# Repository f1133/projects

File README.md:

# projects

A workspace repository for assorted projects.

## About

This repository is a starting point. Each project lives in its own
subdirectory with its own README describing what it does and how to
run it.

## Getting started

```bash
git clone https://github.com/f1133/projects.git
cd projects
```

## Layout

```
projects/
├── README.md
├── hardware/
│   └── g431-can-actuator/   # STM32G431 CAN-FD actuator node (KiCad) + perf-board prototype plans
└── <project-name>/          # one directory per project
```

## Projects

| Project | Description |
|---|---|
| [`hardware/g431-can-actuator`](hardware/g431-can-actuator) | KiCad schematic for a CAN-FD BLDC actuator node: STM32G431CBT6 + DRV8311S three-phase driver, one board per actuator, daisy-chained on a single CAN bus. `proto/` holds the perf-board prototype layouts (placement and wiring pictures, wiring lists, BOMs). |

## License

No license has been chosen yet. Until one is added, all rights are
reserved by the repository owner.

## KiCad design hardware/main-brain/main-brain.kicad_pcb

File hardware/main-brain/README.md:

# main-brain

ESP32-S3 controller for the base. Two I2C devices, two microphones on a shared
clock, the hardware kill line and the power chain — everything that does not
move. 140 x 70 mm.

Generated from the Juno build console's base wiring. Schematic and PCB are
complete through placement, netclasses and design rules. **No copper is
routed.**

## Why the board is this wide

The microphones set it. A6 and A7 sit at x = 5 mm and x = 135 mm, exactly
130 mm apart, because that spacing is what turns two microphones into a
bearing. Both share BCLK and WS and both drive the same data pin; A6 has L/R
tied low and A7 tied high, and that is what makes them stereo.

## Before you route

**The ESP32-S3 Super Mini footprint is unverified.** External sources for this
board were unreachable from the environment this was generated in, so
`ESP32_S3_LEFT` / `ESP32_S3_RIGHT` in `tools/modules.py` hold the conventional
2 x 11 Super Mini arrangement and nothing stronger. Check it against your actual
board before ordering. The schematic is correct regardless — nets are by pin
name — so if the order is wrong, correcting those two lists and re-running
`build.py` is the whole fix. Same applies to the MP1584EN, the mic breakouts and
the I2C modules, though those are more standard.

## Indicators

Two, both XL-3216SURC red 1206, the part you have. D2 sits on the **5 V** rail
rather than 3.3 V so it reports the buck, which is the thing that actually
fails - the S3's own regulator is downstream of it. D3 is a firmware heartbeat
on IO1; the module has an LED on IO48 but it is buried once the board is in the
base.

Series resistors follow the part's 2.4 V forward drop: 470 R on the 5 V rail
and 220 R on the 3.3 V GPIO, both giving about 4-5 mA.

## One part added beyond the console BOM

**D1, a 10 V zener, plus R6.** The console specifies an SI2301-class P-MOSFET
for reverse-polarity protection straight off a 19 V input. That part is rated
around ±8 V gate-source, so an unclamped gate destroys it on first power-up.
R6 pulls the gate down and D1 clamps Vgs. Without these the protection circuit
is the thing that fails.

## One thing worth changing, not changed

The kill line works by pulling the shared EN wire low with Q2, while each node's
PB12 drives that same wire high push-pull. Killing therefore shorts three MCU
outputs to ground through Q2 — within ratings (about 60 mA total, Q2 handles
200 mA) but poor practice, and the node cannot tell it has been killed.

Two clean fixes: a series resistor between PB12 and the EN net on each node
board, or drive PB12 open-drain in firmware. It is left as the console
specifies because changing it is a design decision, not a transcription.

## Pin assignment

Follows `06_electrical.md`. GPIO 3 is left free as a strapping pin. CAN is on
GPIO 5/6 — the docs say "UART or CAN" without saying which is TX, so TX is 5 and
RX is 6; the TWAI controller maps to any GPIO, so swap in firmware if needed.

| GPIO | Use |
|---|---|
| 2 | I2S DIN, both mics |
| 4 | I2S DOUT, to the speaker amp on J4 |
| 5 / 6 | CAN TX / RX |
| 7 | kill line to Q2 |
| 8 / 9 | I2C SDA / SCL |
| 13 | ToF INT |
| 43 / 44 | I2S BCLK / WS |

I2C pull-ups (R1, R2, 2k2) are here and only here — the master end, as the
wiring rules require.

## Ports

| Ref | Port | Pins |
|---|---|---|
| J1 | 19 V barrel jack | star ground lands here |
| J2 | CAN + power to the arm | CANH, CANL, EN, 5 V, GND |
| J3 | 19 V to the arm | +19 V, GND |
| J4 | I2S to the speaker amp | 5 V, GND, DOUT, BCLK, WS |

J4 exists because GPIO 4 is assigned to a speaker amp that the BOM places in the
head while also saying it shares the mic I2S bus — and I2S does not travel over
CAN. The header puts the signal somewhere real; where the amp physically lives
is your call.

## Verification status

ERC and DRC have **not** been run. `tools/check.py` verifies 96 pad nets, 96
schematic stubs against their pin endpoints, courtyard collisions and the board
outline, and every file round-trips through `kiutils`. Run ERC and DRC locally
before ordering.

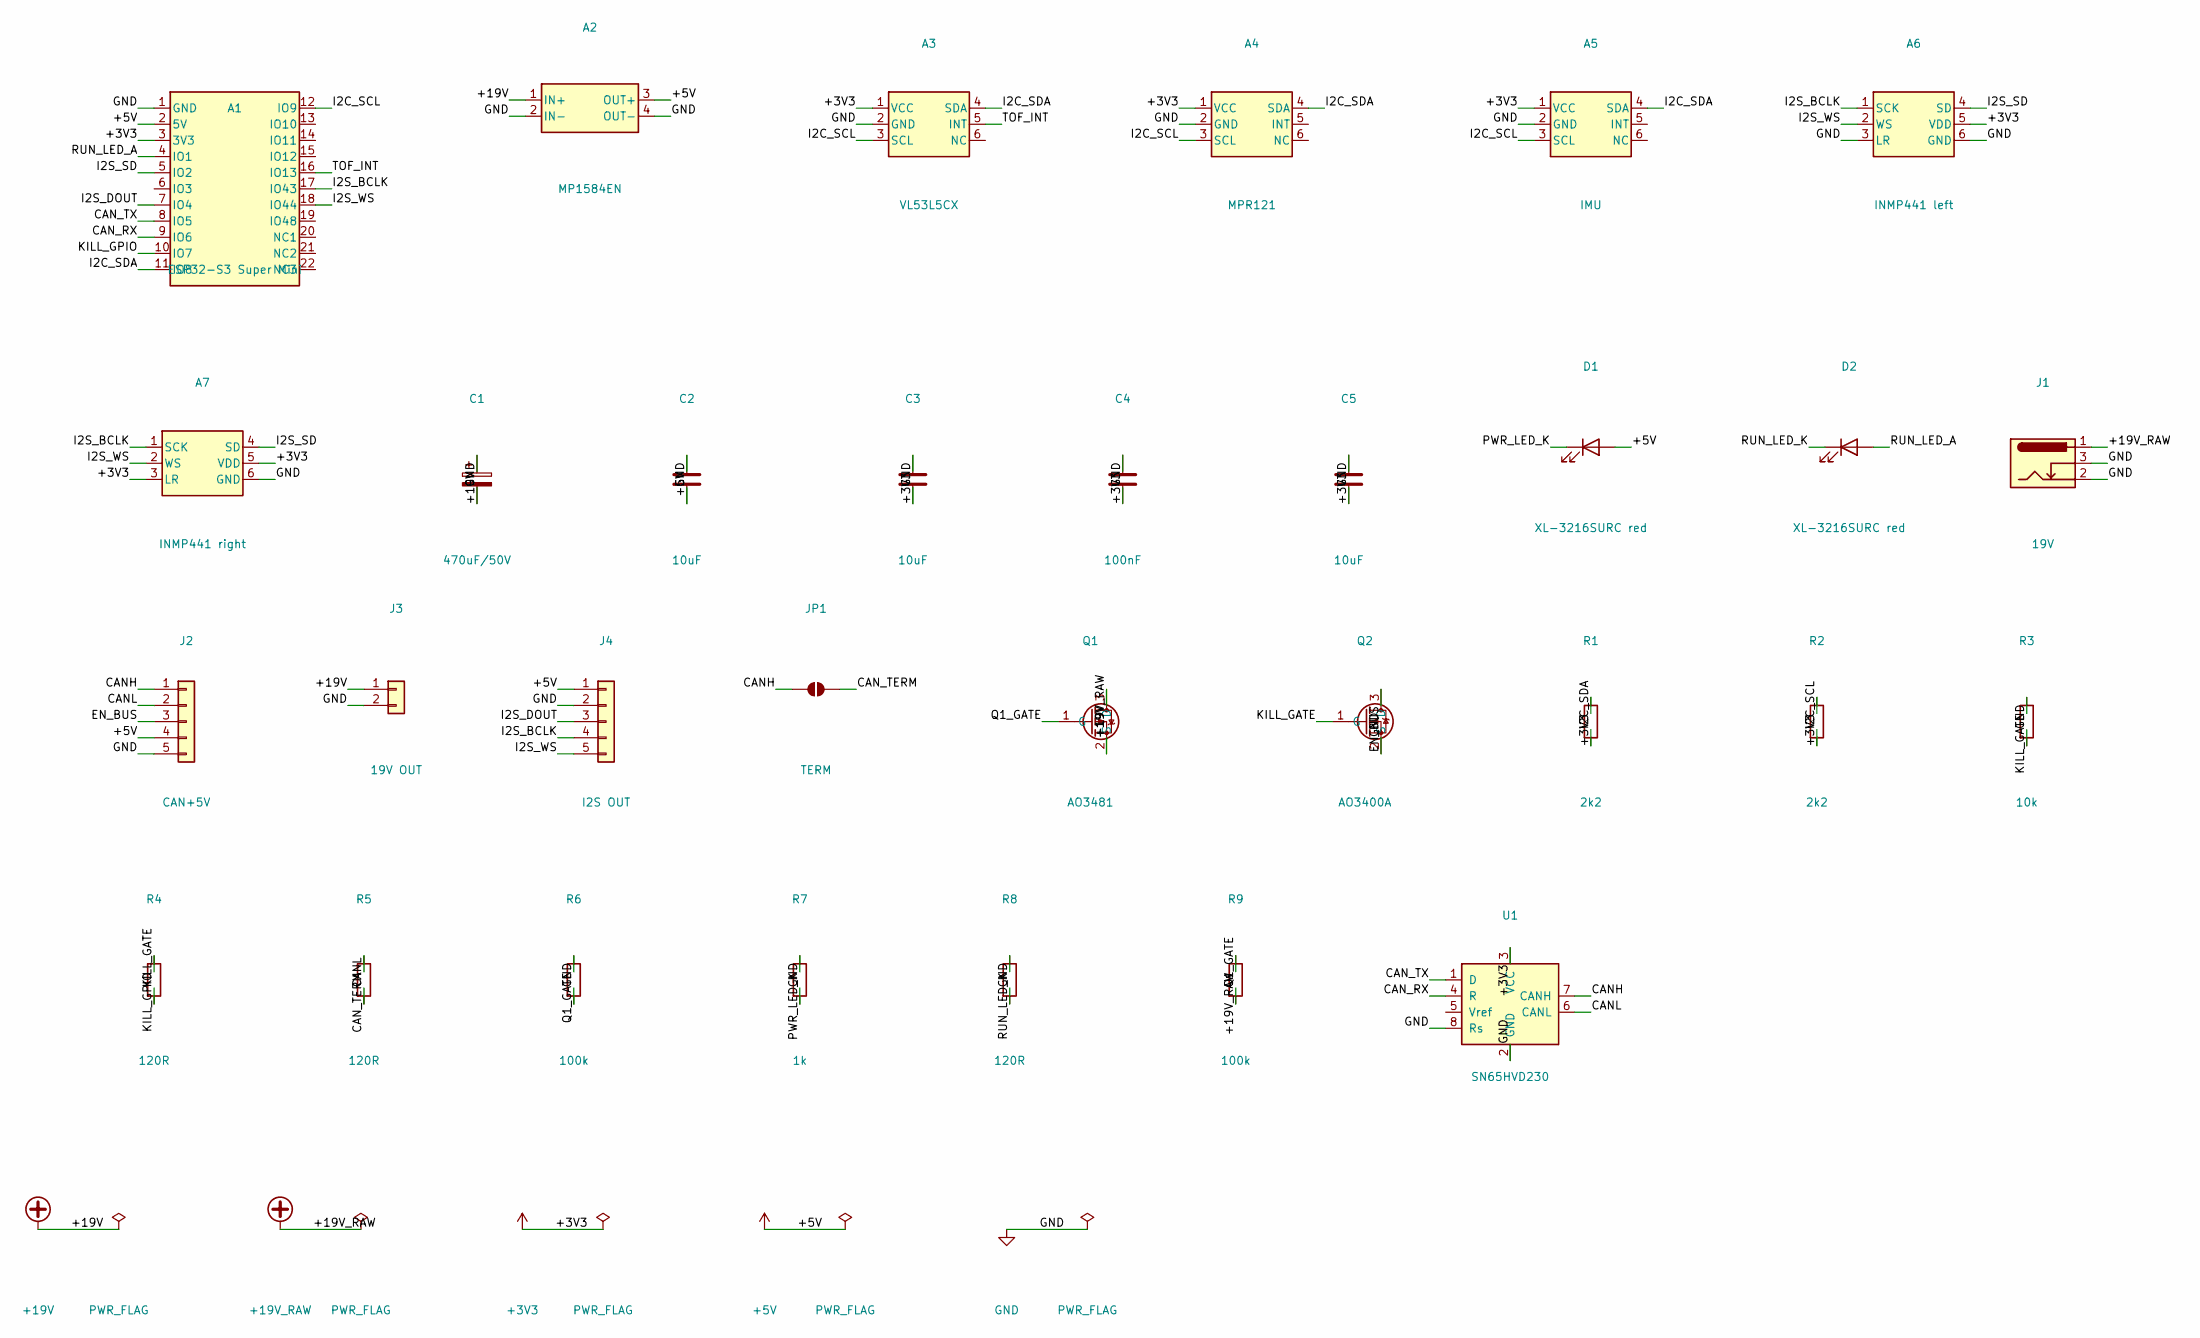
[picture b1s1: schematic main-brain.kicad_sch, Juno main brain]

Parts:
A1: ESP32-S3 Super Mini; ESP32_S3_SuperMini_Socket
A2: MP1584EN; MP1584EN_Module
A3: VL53L5CX; Module_1x06_2.54
A4: MPR121; Module_1x06_2.54
A5: IMU; Module_1x06_2.54
A6: INMP441 left; Module_1x06_2.54
A7: INMP441 right; Module_1x06_2.54
C1: 470uF/50V; CP_Elec_10x10.5
C2, C3, C5: 10uF; C_1206_3216Metric
C4: 100nF; C_1206_3216Metric
D1, D2: XL-3216SURC red; LED_1206_3216Metric
J1: 19V; BarrelJack_CUI_PJ-102AH_Horizontal
J2: CAN+5V; JST_XH_S5B-XH-A_1x05_P2.50mm_Horizontal
J3: 19V OUT; JST_VH_S2P-VH_1x02_P3.96mm_Horizontal
J4: I2S OUT; PinHeader_1x05_P2.54mm_Vertical
JP1: TERM; SolderJumper-2_P1.3mm_Open_Pad1.0x1.5mm
Q1: AO3481; SOT-23
Q2: AO3400A; SOT-23
R1, R2: 2k2; R_1206_3216Metric
R3: 10k; R_1206_3216Metric
R4, R5, R8: 120R; R_1206_3216Metric
R6, R9: 100k; R_1206_3216Metric
R7: 1k; R_1206_3216Metric
U1: SN65HVD230; SOIC-8_3.9x4.9mm_P1.27mm

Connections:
+3V3: A1.3 (3V3), A3.1 (VCC), A4.1 (VCC), A5.1 (VCC), A6.5 (VDD), A7.3 (LR), A7.5 (VDD), C3.1, C4.1, C5.1, R1.1, R2.1, U1.3 (VCC)
+5V: A1.2 (5V), A2.3 (OUT+), C2.1, D1.2 (A), J2.4, J4.1
+19V: A2.1 (IN+), C1.1, J3.1, Q1.3 (D)
+19V_RAW: J1.1, Q1.2 (S), R9.1
CANH: J2.1, JP1.1 (A), U1.7 (CANH)
CANL: J2.2, R5.2, U1.6 (CANL)
CAN_RX: A1.9 (IO6), U1.4 (R)
CAN_TERM: JP1.2 (B), R5.1
CAN_TX: A1.8 (IO5), U1.1 (D)
EN_BUS: J2.3, Q2.3 (D)
GND: A1.1 (GND), A2.2 (IN-), A2.4 (OUT-), A3.2 (GND), A4.2 (GND), A5.2 (GND), A6.3 (LR), A6.6 (GND), A7.6 (GND), C1.2, C2.2, C3.2, C4.2, C5.2, J1.2, J1.3, J2.5, J3.2, J4.2, Q2.2 (S), R3.2, R6.2, R7.2, R8.2, U1.2 (GND), U1.8 (Rs)
I2C_SCL: A1.12 (IO9), A3.3 (SCL), A4.3 (SCL), A5.3 (SCL), R2.2
I2C_SDA: A1.11 (IO8), A3.4 (SDA), A4.4 (SDA), A5.4 (SDA), R1.2
I2S_BCLK: A1.17 (IO43), A6.1 (SCK), A7.1 (SCK), J4.4
I2S_DOUT: A1.7 (IO4), J4.3
I2S_SD: A1.5 (IO2), A6.4 (SD), A7.4 (SD)
I2S_WS: A1.18 (IO44), A6.2 (WS), A7.2 (WS), J4.5
KILL_GATE: Q2.1 (G), R3.1, R4.2
KILL_GPIO: A1.10 (IO7), R4.1
PWR_LED_K: D1.1 (K), R7.1
Q1_GATE: Q1.1 (G), R6.1, R9.2
RUN_LED_A: A1.4 (IO1), D2.2 (A)
RUN_LED_K: D2.1 (K), R8.1
TOF_INT: A1.16 (IO13), A3.5 (INT)

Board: 2 copper layers, 31 parts (0 on the bottom side), 24 nets, no tracks yet.

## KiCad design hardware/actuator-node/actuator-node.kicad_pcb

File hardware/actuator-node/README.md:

# actuator-node

STM32G431CBT6 CAN-FD joint controller. One per joint; the boards daisy-chain on
a single CAN bus and are addressed by three solder jumpers. 70 x 60 mm.

Parts are placed by functional block - see `placement.svg` for the colour-coded
map. Each block keeps its own passives: the CAN transceiver with its
termination and decoupling, the crystal with its two load caps, each INA240
with its shunt, the LDO with its input and output caps. Parts with an
electrical reason to hug something else are placed against it rather than
merely in the same region, and `tools/check.py` enforces the distances as
courtyard-edge gaps, not centre to centre: the crystal within 6 mm of the MCU,
its two load caps within 2 mm of the crystal, the MCU's 100 nF decoupling
within 5 mm, everything else within 12 mm.

Generated from the Juno build console. Schematic and PCB are complete through
placement, netclasses and design rules. **No copper is routed** — that is yours.

## Before you route: three things to check

**1. The driver module is measured, and it is A1, not M1.** Its footprint and
symbol are read at build time from the vendor's own EasyEDA exports in
`vendor/`: the PCB export gives pad positions, sizes and drills, and the
schematic export resolves that PCB's anonymous `U1_nn` nets to real signals.
19 pads — 15 pins plus 4 mounting holes — over 22.6 × 17.9 mm.

The reference is **A1** rather than M1, because the module's own silkscreen
calls its three motor pads M1/M2/M3 and `("M1", "M1")` in a netlist helps
nobody.

| Pin | Signal | Goes to | Pin | Signal | Goes to |
|---|---|---|---|---|---|
| 1 | EN | PB12, the kill line | 9 | GND | GND |
| 2 | IN3 | PA10, TIM1_CH3 | 10 | 3V3 | **nothing — see below** |
| 3 | IN2 | PA9, TIM1_CH2 | 11 | GND | GND |
| 4 | IN1 | PA8, TIM1_CH1 | 12 | VM | +19 V |
| 5 | GND | GND | 13 | M1 | phase A, through shunt R1 |
| 6 | nFlt | PB4 | 14 | M2 | phase B, through shunt R2 |
| 7 | nSlp | open | 15 | M3 | phase C |
| 8 | nRes | open | | | |

**2. Pin 10 is an output, and must stay unconnected.** The vendor schematic
shows it is DRV8313 pin 15, `V3P3OUT` — the driver's internal 3.3 V regulator.
An earlier revision of this project tied it to the carrier's 3.3 V rail on the
assumption it was a supply input, which would have connected the AMS1117's
output to the module's regulator. `tools/check.py` now fails the build if it
ever reappears on a net.

That same regulator feeds the module's own pull-ups on nSlp, nRes and nFlt,
which is why those three idle in the running state with nothing attached — the
driver comes out of sleep and reset by itself once VM is present.

**3. An earlier export was the wrong board.** The first EasyEDA file supplied
was a "step mini": a quad half-bridge with IN1–IN4 and four outputs. The board
on the bench is the SimpleFOC Mini v1.0 (DRV8313, three phases, dated 04/22),
and everything here is built from its export instead. The checker refuses any
net mentioning `IN4` or `OUT4` so the two cannot be confused again.

Still print the footprint at 1:1 and sit the real module on it before ordering.
Geometry is measured now rather than guessed, so this is a confirmation rather
than a discovery — but it is the one check that catches a mirrored footprint.

**2. The INA240 pinout.** The console and the KiCad symbol disagree: the console
says pin 1 IN+, pin 4 REF1, pin 7 NC; KiCad says pin 1 IN−, pin 4 GND, pin 7
REF1. This is resolved in KiCad's favour, because the console's pin numbers are
demonstrably unreliable (its MCU diagram gives both NRST and VSSA as pin 7) and
two independent sources corroborate pin 4 = GND and pin 7 = REF1. It matters:
taking the console's numbering would have driven the chip's ground pin to 3V3.
Worth one look at the datasheet, which you can open locally.

**3. BOOT0 does not exist as its own pin here.** On the LQFP-48 G431 it is
multiplexed onto PB8, which the pin assignment gives to FDCAN1_RX. The console's
MCU diagram draws a standalone BOOT0 pin with a pull-down; that pin is not on
the package. R6 is therefore a pull-down on PB8 itself.

By factory default `nBOOT_SEL = 1` and the pin is ignored, so this is latent
rather than broken. But if it is ever cleared, an idle (recessive) bus holds the
transceiver's R output high at reset and the part boots the ROM bootloader
instead of your firmware — the same hot-plug trap your own notes call out for
the C3's straps. FDCAN1 can move to PA11/PA12, which are otherwise unused, if
you want PB8 free. Settle it in CubeMX (chunk A4) before etching.

## Deviations from the console

| | |
|---|---|
| **Encoder** | Motor-mounted, so a 4-pin header (3V3 GND SCL SDA) at J6 replaces the AS5600 soldered through the board centre. |
| **Two layers, not one** | See `../docs/fabrication.md`. The 0 R crossover jumpers JP1–JP8 in the console BOM are not needed and are gone. |
| **470 µF moved** | The console puts it where the CAN-ext connector is; there they are on opposite faces, here both are front-side. |
| **LEDs** | Two, both XL-3216SURC red 1206 (the part you have). D1 is the status LED on PC13; D2 is new and reports the 3.3 V rail directly, so a dead board tells you whether the LDO is up before firmware is involved. Series resistors are 120 R: at Vf 2.4 V there is only 0.9 V of headroom on a 3.3 V rail, so the value sets the current sharply - 120 R gives 7.5 mA, well inside both the LED's 20 mA and what a G431 pin sources. |
| **Shunt sense polarity** | The console's drawing and its caption contradict each other. Taken as drawn: IN+ driver side, IN− motor side, so output rises above mid-rail for current flowing driver → motor. A firmware sign constant, not a wiring hazard. |

## Floorplan and ports

Every connector in the order is a **right-angle** part, which changed the
layout for the better: the cable leaves in the plane of the board instead of
standing up off it, so nothing competes with the gearbox for height. The
rotation on each one is what points the cable outward — 0° for the bottom edge,
180° for the top, 90° right, 270° left.

Three rules set the positions:

- **The two CAN connectors sit on opposite edges**, J2 left and J3 right, so a
  harness enters one side of a joint and leaves the other. A daisy chain should
  look like a daisy chain.
- **Everything that goes to the motor leaves together** along the bottom edge:
  phases (J1), stator NTC (J7), encoder (J6) and the SPI upgrade header (J8).
  One loom, one direction.
- **Power and debug take the top**, J4 and J5, away from the motor loom.

All eight ports are on the perimeter, none closer than 1.1 mm to an edge.

| Ref | Port | Pins | Connector | Edge |
|---|---|---|---|---|
| J1 | Motor phases | A, B, C | 3 pin XH, right angle | bottom |
| J2 | CAN in | CANH, CANL, EN, 5 V, GND | 5 pin XH, right angle | left |
| J3 | CAN ext, in parallel with J2 | CANH, CANL, EN, 5 V, GND | 5 pin XH, right angle | right |
| J4 | 19 V in | +19 V, GND | 2 pin VH, right angle | top |
| J5 | SWD | 3V3, SWDIO, SWCLK, NRST, GND | 1×5 header 2.54 | top |
| J6 | Encoder | 3V3, GND, SCL, SDA | 1×4 header 2.54 | bottom |
| J7 | Motor NTC | sense, return, GND | 3 pin XH, right angle | bottom |
| J8 | SPI (spare) | 3V3, GND, SCK, MISO, MOSI, CS | 1×6 header 2.54 | bottom |

NRST is on the SWD header deliberately. Without it the ST-Link cannot do
connect-under-reset, and firmware that disables SWD early bricks the chip.

J7 is a 3-pin body because no 2-pin XH is stocked. Pin 3 is grounded, so the
sense wire can be twisted against its own return on the way out of the stator
instead of sharing a path with the phase currents.

J8 is unpopulated silicon made available: SPI1 is otherwise unused, and it is
the exit route when the AS5600's I²C read time (~112 µs) becomes the thing
limiting the position loop. See `../docs/capabilities.md`.

## Height under the gearbox

The gearbox covers a Ø48 circle on the **back** face with 5.5 mm of clearance.
Everything on this board is front-mounted; the only thing that reaches through
is a through-hole leg and its fillet, about 1.5 mm. Comfortable.

Note that the console labels that circle Ø48 but draws it at Ø43.6. The keepout
marked on `Cmts.User` follows the drawing. Measure the real gearbox.

## Verification status

ERC and DRC have **not** been run — KiCad was not available in the environment
this was generated in. What has been checked, by `tools/check.py`:

- every pad's net matches the spec, 191 of them;
- every schematic stub actually touches its pin's connection point and carries
  the right label, so nothing looks connected while being open;
- no two courtyards overlap and everything is inside the outline;
- every file round-trips through `kiutils`.

Open it, run ERC and DRC, and expect one intentional courtyard note: the Mini
sits 8.5 mm above the MCU on headers, so its footprint deliberately has two
separate courtyards with the MCU in the gap.

## Regenerating

```sh
cd ../tools && KICAD_LIBS=<dir with kicad-symbols and kicad-footprints at 8.0.9> \
  python3 build.py && python3 check.py
```

Once you start editing in KiCad the `.kicad_*` files become the source of truth
and the generator is history. Until then, change `spec.py` rather than the
schematic — the checker verifies the board against it.

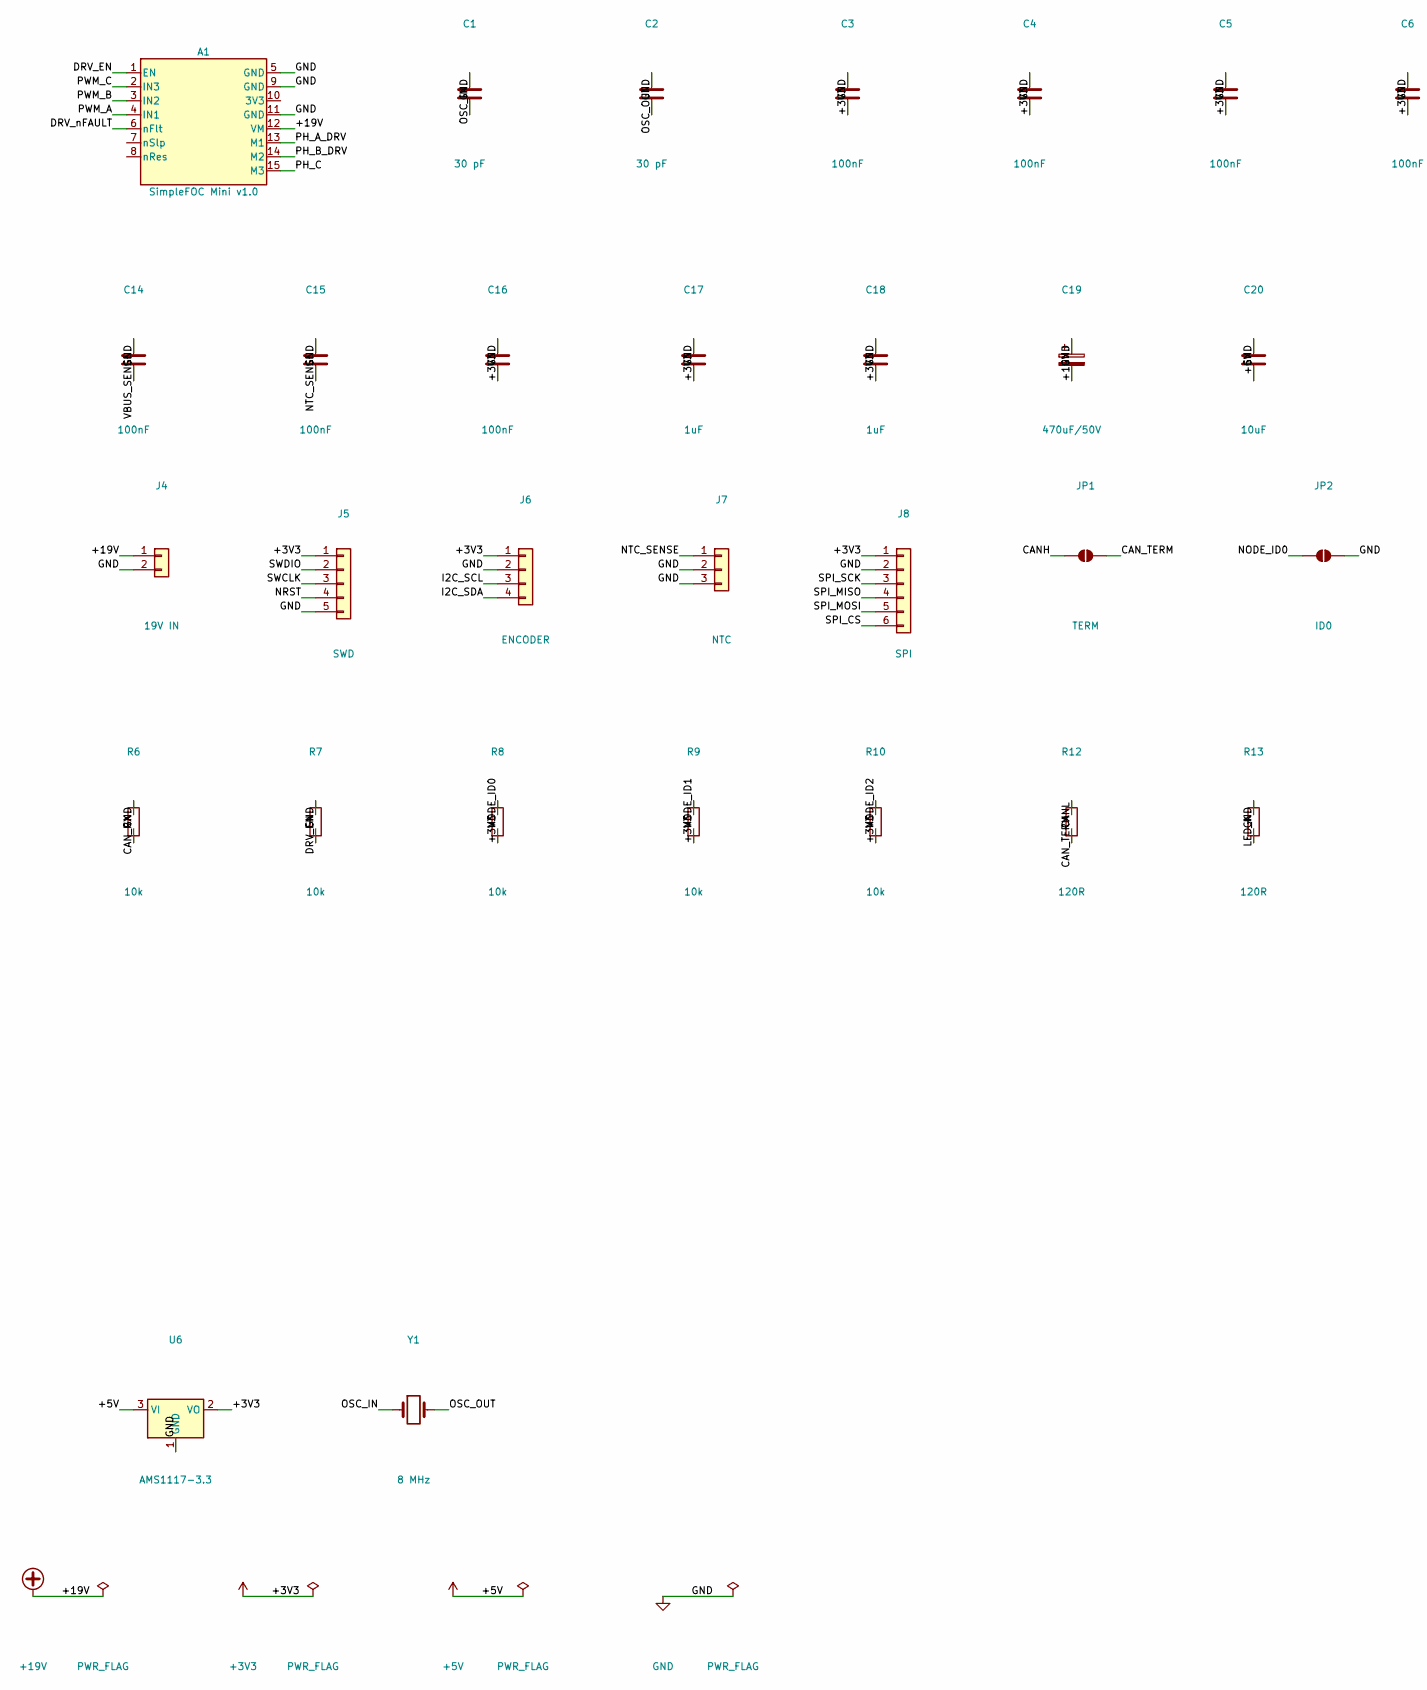
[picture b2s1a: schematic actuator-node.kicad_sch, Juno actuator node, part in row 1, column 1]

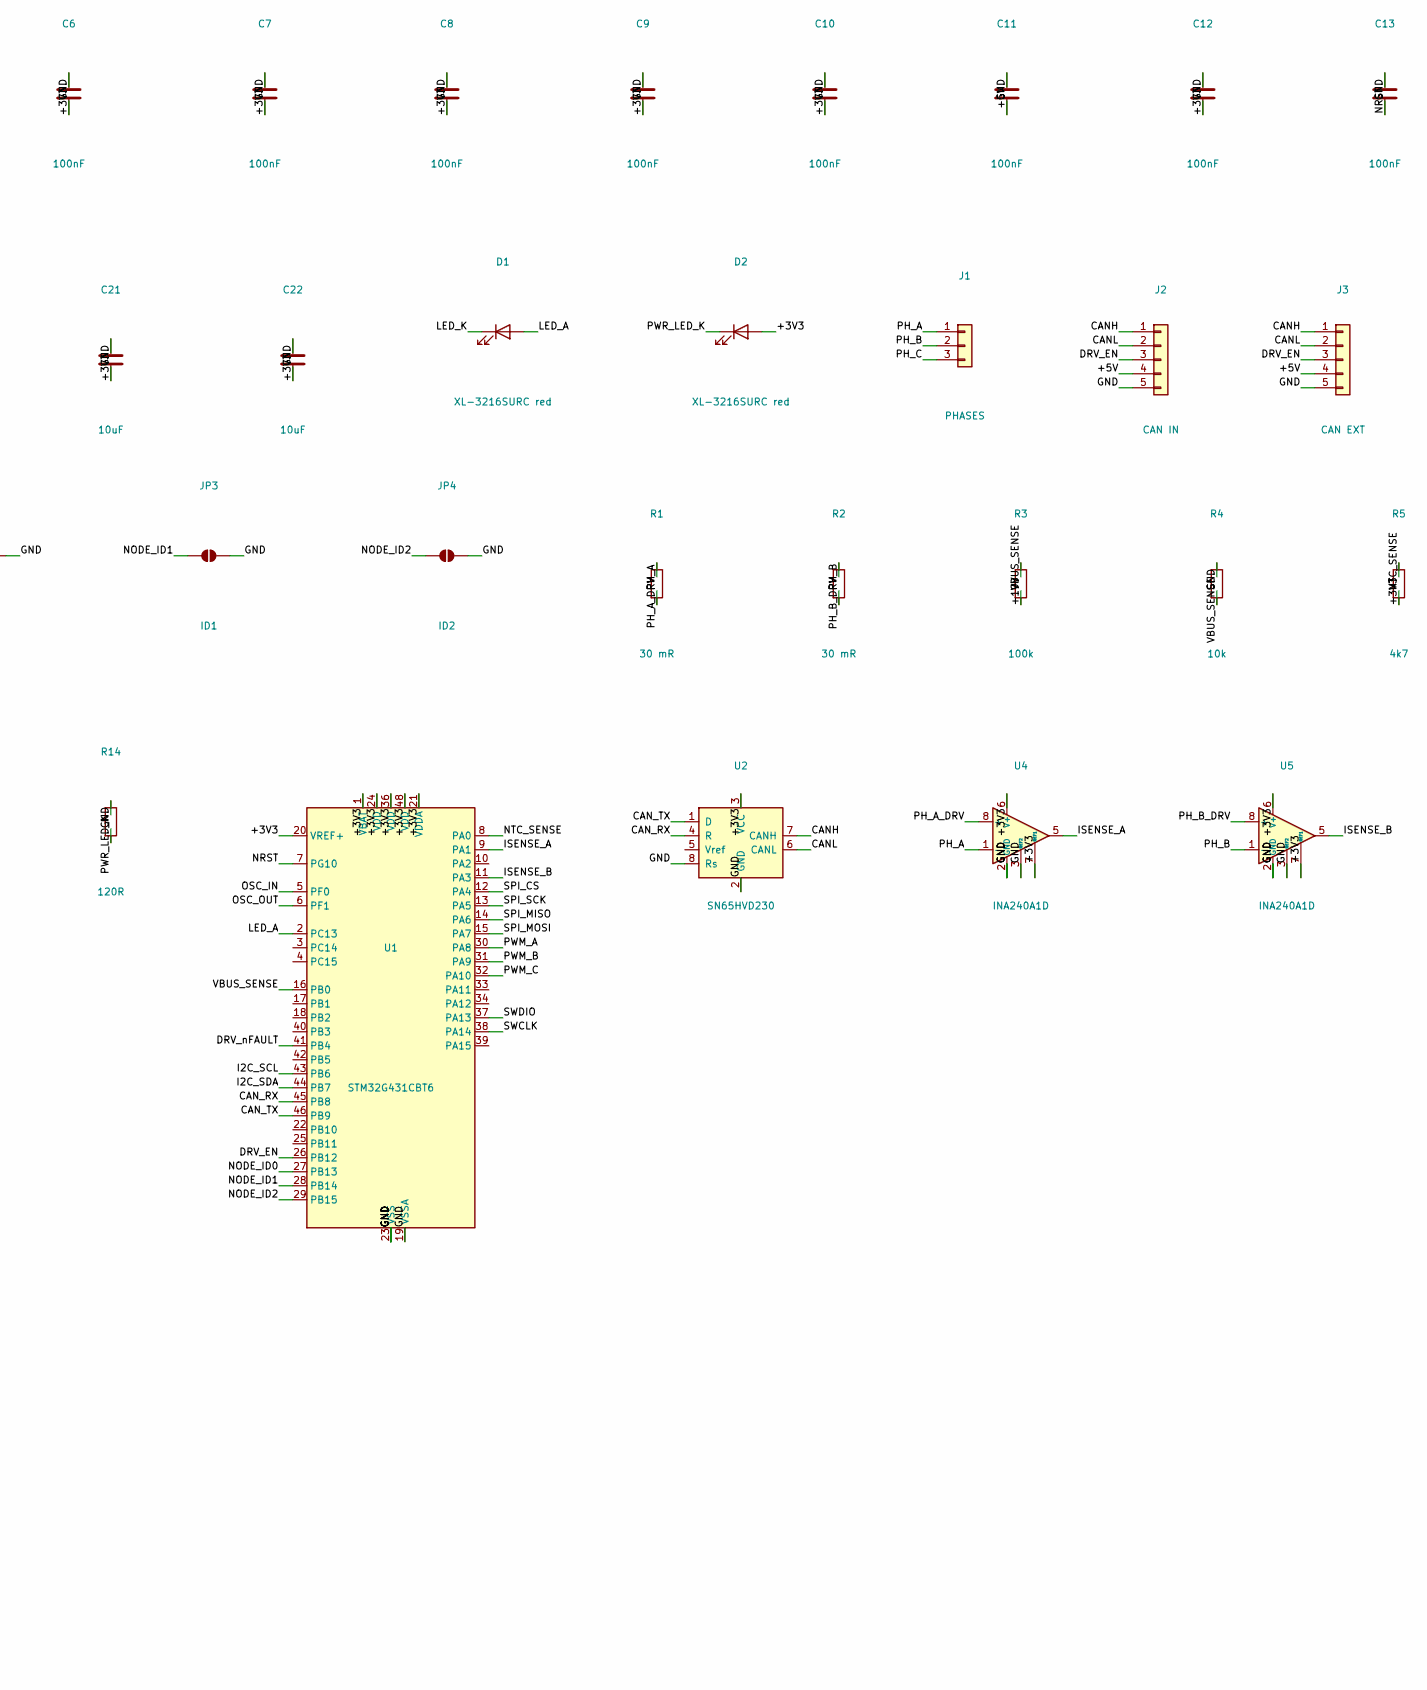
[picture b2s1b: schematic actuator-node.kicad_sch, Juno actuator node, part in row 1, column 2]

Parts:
A1: SimpleFOC Mini v1.0; SimpleFOC_Mini_Socket
C1, C2: 30 pF; C_1206_3216Metric
C3, C4, C5, C6, C7, C8, C9, C10, C11, C12, C13, C14, C15, C16: 100nF; C_1206_3216Metric
C17, C18: 1uF; C_1206_3216Metric
C19: 470uF/50V; CP_Elec_10x10.5
C20, C21, C22: 10uF; C_1206_3216Metric
D1, D2: XL-3216SURC red; LED_1206_3216Metric
J1: PHASES; JST_XH_S3B-XH-A_1x03_P2.50mm_Horizontal
J2: CAN IN; JST_XH_S5B-XH-A_1x05_P2.50mm_Horizontal
J3: CAN EXT; JST_XH_S5B-XH-A_1x05_P2.50mm_Horizontal
J4: 19V IN; JST_VH_S2P-VH_1x02_P3.96mm_Horizontal
J5: SWD; PinHeader_1x05_P2.54mm_Vertical
J6: ENCODER; PinHeader_1x04_P2.54mm_Vertical
J7: NTC; JST_XH_S3B-XH-A_1x03_P2.50mm_Horizontal
J8: SPI; PinHeader_1x06_P2.54mm_Vertical
JP1: TERM; SolderJumper-2_P1.3mm_Open_Pad1.0x1.5mm
JP2: ID0; SolderJumper-2_P1.3mm_Open_Pad1.0x1.5mm
JP3: ID1; SolderJumper-2_P1.3mm_Open_Pad1.0x1.5mm
JP4: ID2; SolderJumper-2_P1.3mm_Open_Pad1.0x1.5mm
R1, R2: 30 mR; R_1206_3216Metric
R3: 100k; R_1206_3216Metric
R4, R6, R7, R8, R9, R10: 10k; R_1206_3216Metric
R5: 4k7; R_1206_3216Metric
R12, R13, R14: 120R; R_1206_3216Metric
U1: STM32G431CBT6; LQFP-48_7x7mm_P0.5mm
U2: SN65HVD230; SOIC-8_3.9x4.9mm_P1.27mm
U4, U5: INA240A1D; SOIC-8_3.9x4.9mm_P1.27mm
U6: AMS1117-3.3; SOT-223-3_TabPin2
Y1: 8 MHz; Crystal_SMD_HC49-SD_HandSoldering

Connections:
+3V3: C3.1, C4.1, C5.1, C6.1, C7.1, C8.1, C9.1, C10.1, C12.1, C16.1, C17.1, C18.1, C21.1, C22.1, D2.2 (A), J5.1, J6.1, J8.1, R5.1, R8.1, R9.1, R10.1, U1.1 (VBAT), U1.20 (VREF+), U1.21 (VDDA), U1.24 (VDD), U1.36 (VDD), U1.48 (VDD), U2.3 (VCC), U4.6 (V+), U4.7 (REF1), U5.6 (V+), U5.7 (REF1), U6.2 (VO)
+5V: C11.1, C20.1, J2.4, J3.4, U6.3 (VI)
+19V: A1.12 (VM), C19.1, J4.1, R3.1
CANH: J2.1, J3.1, JP1.1 (A), U2.7 (CANH)
CANL: J2.2, J3.2, R12.2, U2.6 (CANL)
CAN_RX: R6.1, U1.45 (PB8), U2.4 (R)
CAN_TERM: JP1.2 (B), R12.1
CAN_TX: U1.46 (PB9), U2.1 (D)
DRV_EN: A1.1 (EN), J2.3, J3.3, R7.1, U1.26 (PB12)
DRV_nFAULT: A1.6 (nFlt), U1.41 (PB4)
GND: A1.5 (GND), A1.9 (GND), A1.11 (GND), C1.2, C2.2, C3.2, C4.2, C5.2, C6.2, C7.2, C8.2, C9.2, C10.2, C11.2, C12.2, C13.2, C14.2, C15.2, C16.2, C17.2, C18.2, C19.2, C20.2, C21.2, C22.2, J2.5, J3.5, J4.2, J5.5, J6.2, J7.2, J7.3, J8.2, JP2.2 (B), JP3.2 (B), JP4.2 (B), R4.2, R6.2, R7.2, R13.2, R14.2, U1.19 (VSSA), U1.23 (VSS), U1.35 (VSS), U1.47 (VSS), U2.2 (GND), U2.8 (Rs), U4.2 (GND), U4.3 (REF2), U4.4 (GND), U5.2 (GND), U5.3 (REF2), U5.4 (GND), U6.1 (GND)
I2C_SCL: J6.3, U1.43 (PB6)
I2C_SDA: J6.4, U1.44 (PB7)
ISENSE_A: U1.9 (PA1), U4.5
ISENSE_B: U1.11 (PA3), U5.5
LED_A: D1.2 (A), U1.2 (PC13)
LED_K: D1.1 (K), R13.1
NODE_ID0: JP2.1 (A), R8.2, U1.27 (PB13)
NODE_ID1: JP3.1 (A), R9.2, U1.28 (PB14)
NODE_ID2: JP4.1 (A), R10.2, U1.29 (PB15)
NRST: C13.1, J5.4, U1.7 (PG10)
NTC_SENSE: C15.1, J7.1, R5.2, U1.8 (PA0)
OSC_IN: C1.1, U1.5 (PF0), Y1.1
OSC_OUT: C2.1, U1.6 (PF1), Y1.2
PH_A: J1.1, R1.2, U4.1 (-)
PH_A_DRV: A1.13 (M1), R1.1, U4.8 (+)
PH_B: J1.2, R2.2, U5.1 (-)
PH_B_DRV: A1.14 (M2), R2.1, U5.8 (+)
PH_C: A1.15 (M3), J1.3
PWM_A: A1.4 (IN1), U1.30 (PA8)
PWM_B: A1.3 (IN2), U1.31 (PA9)
PWM_C: A1.2 (IN3), U1.32 (PA10)
PWR_LED_K: D2.1 (K), R14.1
SPI_CS: J8.6, U1.12 (PA4)
SPI_MISO: J8.4, U1.14 (PA6)
SPI_MOSI: J8.5, U1.15 (PA7)
SPI_SCK: J8.3, U1.13 (PA5)
SWCLK: J5.3, U1.38 (PA14)
SWDIO: J5.2, U1.37 (PA13)
VBUS_SENSE: C14.1, R3.2, R4.1, U1.16 (PB0)

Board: 2 copper layers, 56 parts (0 on the bottom side), 40 nets, no tracks yet.

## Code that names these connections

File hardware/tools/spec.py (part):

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    R("R5", "4k7"),    # NTC pull-up to 3V3

    # --- pull resistors -----------------------------------------------------
    R("R6", "10k"),    # PB8 / BOOT0 pull-down, see CONFLICT-2
    R("R7", "10k"),    # driver EN pull-down: unpowered controller means motors off
    R("R8", "10k"), R("R9", "10k"), R("R10", "10k"),   # node ID pull-ups
    R("R12", "120R"),  # CAN termination, behind a solder jumper
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    # 120 R gives 7.5 mA - bright, inside the LED's 20 mA and well inside what
    # a G431 pin will source - and it is a value already in stock.
    dict(ref="D1", value="XL-3216SURC red", lib=DEV, sym="LED", fp=LED_1206,
         note="status / functioning, driven from PC13"),
    # ADDED: the console has one LED. A rail that is simply on or off is the
    # first thing you want to see when a board does not enumerate, so the 3V3
    # rail gets its own indicator that owes nothing to firmware.
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         note="Thermistor bead lives inside the stator, not on the board. "
              "A 3-pin body because no 2-pin XH is stocked; pin 3 is grounded "
              "so the sense wire can be twisted against its own return."),
    # SPI1 is entirely free - PA4 to PA7 are unused - so the upgrade path to an
    # SPI encoder (AS5047P, MA730, TLE5012B) or an SPI-configured driver costs
    # one header and no re-assignment. SPI2 collides with the driver EN and the
    # node-ID jumpers; SPI3 collides with the driver fault line.
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#   Still worth one look at the datasheet before you order.
#
# CONFLICT-2  BOOT0 does not exist as a separate pin on the LQFP-48 G431.
#   It is multiplexed onto PB8, which the pin assignment gives to FDCAN1_RX.
#   The console's MCU diagram draws a standalone BOOT0 pin with a pull-down;
#   that pin is not there. R6 is therefore a pull-down on PB8 itself.
#   By factory default nBOOT_SEL=1 and the pin is ignored, so this is latent
#   rather than broken - but if nBOOT_SEL is ever cleared, an idle (recessive)
#   bus holds the transceiver's R output high at reset and the part boots the
#   ROM bootloader instead of your firmware. FDCAN1 can move to PA11/PA12,
#   which are otherwise unused, if you want PB8 free. Settle it in CubeMX (A4).
#
# CONFLICT-3  Shunt sense polarity. The console's drawing wires IN+ to the
#   driver side of the shunt; its caption says IN+ goes to the motor side.
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#   constant, not a wiring hazard - the note in the console agrees ("swapped,
#   the current reads negative").
#
# NRST is pin 7 / PG10 on this package; KiCad names it PG10.
# ---------------------------------------------------------------------------

# CONFLICT-4  The driver module, twice over.
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    ],

    # --- motor drive --------------------------------------------------------
    "PWM_A": [("U1", "PA8"), ("A1", "IN1")],
    "PWM_B": [("U1", "PA9"), ("A1", "IN2")],
    "PWM_C": [("U1", "PA10"), ("A1", "IN3")],
    # EN is the hardware kill line: it leaves on both CAN connectors so the
    # brain can pull every driver down at once, and R7 holds it off unpowered.
    "DRV_EN": [("U1", "PB12"), ("A1", "EN"), ("J2", "Pin_3"), ("J3", "Pin_3"), ("R7", "1")],

    # --- phases and current sense ------------------------------------------
    "PH_A_DRV": [("A1", "M1"), ("R1", "1"), ("U4", "+")],
    "PH_A": [("R1", "2"), ("J1", "Pin_1"), ("U4", "-")],
    "PH_B_DRV": [("A1", "M2"), ("R2", "1"), ("U5", "+")],
    "PH_B": [("R2", "2"), ("J1", "Pin_2"), ("U5", "-")],
    "PH_C": [("A1", "M3"), ("J1", "Pin_3")],
    # The module brings nFAULT out with its own pull-up. PB4 is free and this
    # is the difference between a driver that has tripped and a motor that is
    # merely not moving, so it is worth the pin.
    "DRV_nFAULT": [("A1", "nFlt"), ("U1", "PB4")],
    "ISENSE_A": [("U4", "~"), ("U1", "PA1")],
    "ISENSE_B": [("U5", "~"), ("U1", "PA3")],

    # --- encoder (motor-mounted, on a cable) --------------------------------
    "I2C_SCL": [("U1", "PB6"), ("J6", "Pin_3")],
    # --- spare SPI1, for an encoder or driver upgrade -----------------------
    "SPI_SCK": [("U1", "PA5"), ("J8", "Pin_3")],
    "SPI_MISO": [("U1", "PA6"), ("J8", "Pin_4")],
    "SPI_MOSI": [("U1", "PA7"), ("J8", "Pin_5")],
    "SPI_CS": [("U1", "PA4"), ("J8", "Pin_6")],
    "I2C_SDA": [("U1", "PB7"), ("J6", "Pin_4")],

    # --- CAN ----------------------------------------------------------------
    "CAN_RX": [("U1", "PB8"), ("U2", "R"), ("R6", "1")],
    "CAN_TX": [("U1", "PB9"), ("U2", "D")],
    "CANH": [("U2", "CANH"), ("J2", "Pin_1"), ("J3", "Pin_1"), ("JP1", "A")],
    "CANL": [("U2", "CANL"), ("J2", "Pin_2"), ("J3", "Pin_2"), ("R12", "2")],
    "CAN_TERM": [("JP1", "B"), ("R12", "1")],

    # --- analog inputs ------------------------------------------------------
    "VBUS_SENSE": [("R3", "2"), ("R4", "1"), ("U1", "PB0"), ("C14", "1")],
    "NTC_SENSE": [("R5", "2"), ("J7", "Pin_1"), ("U1", "PA0"), ("C15", "1")],

    # --- node address -------------------------------------------------------
    "NODE_ID0": [("U1", "PB13"), ("R8", "2"), ("JP2", "A")],
    "NODE_ID1": [("U1", "PB14"), ("R9", "2"), ("JP3", "A")],
    "NODE_ID2": [("U1", "PB15"), ("R10", "2"), ("JP4", "A")],

    # --- debug and clock ----------------------------------------------------
    "SWDIO": [("U1", "PA13"), ("J5", "Pin_2")],
    "SWCLK": [("U1", "PA14"), ("J5", "Pin_3")],
    "NRST": [("U1", "PG10"), ("J5", "Pin_4"), ("C13", "1")],
    "OSC_IN": [("U1", "PF0"), ("Y1", "1"), ("C1", "1")],
    "OSC_OUT": [("U1", "PF1"), ("Y1", "2"), ("C2", "1")],

    # --- status -------------------------------------------------------------
    "LED_A": [("U1", "PC13"), ("D1", "A")],
    "LED_K": [("D1", "K"), ("R13", "1")],
    "PWR_LED_K": [("D2", "K"), ("R14", "1")],
}
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
    # --- I2S: both mics share the clock, both drive the same data pin -------
    "I2S_SD": [("A1", "IO2"), ("A6", "SD"), ("A7", "SD")],
    "I2S_BCLK": [("A1", "IO43"), ("A6", "SCK"), ("A7", "SCK"), ("J4", "Pin_4")],
    "I2S_WS": [("A1", "IO44"), ("A6", "WS"), ("A7", "WS"), ("J4", "Pin_5")],
    "I2S_DOUT": [("A1", "IO4"), ("J4", "Pin_3")],

    # --- hardware kill ------------------------------------------------------
    "KILL_GPIO": [("A1", "IO7"), ("R4", "1")],
    "KILL_GATE": [("R4", "2"), ("Q2", "G"), ("R3", "1")],
    "EN_BUS": [("Q2", "D"), ("J2", "Pin_3")],

    # --- indicators ---------------------------------------------------------
    "PWR_LED_K": [("D1", "K"), ("R7", "1")],
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    # --- CAN ----------------------------------------------------------------
    "CAN_TX": [("A1", "IO5"), ("U1", "D")],
    "CAN_RX": [("A1", "IO6"), ("U1", "R")],
    "CANH": [("U1", "CANH"), ("J2", "Pin_1"), ("JP1", "A")],
    "CANL": [("U1", "CANL"), ("J2", "Pin_2"), ("R5", "2")],
    "CAN_TERM": [("JP1", "B"), ("R5", "1")],
}

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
